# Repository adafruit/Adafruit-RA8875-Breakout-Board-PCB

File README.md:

## Adafruit RA8875 Driver Board for 40-pin TFT Touch Displays - 800x480 Max PCB

<a href="http://www.adafruit.com/products/1590"><br/>
Click here to purchase one from the Adafruit shop</a>

PCB files for the Adafruit RA8875 Driver Board for 40-pin TFT Touch Displays - 800x480 Max. Format is EagleCAD schematic and board layout
* https://www.adafruit.com/product/1590

### Description

Have you gazed longingly at large TFT displays - you know what I'm talking about here, 4", 5" or 7" TFTs with up to 800x480 pixels. Then you look at your Arduino. You love your Arduino (you really do!) but there's no way it can control a display like that, one that requires 60Hz refresh and 4 MHz pixel clocking. Heck, it doesn't even have enough pins. I suppose you could move to ARM core processors with TTL display drivers built in but you've already got all these shields working and anyways you like small micros you've got.

What if I told you there was a driver chip that could fulfill those longings? A chip that can control up 800x480 displays, and heck, a resistive touchscreen as well. All you need to give up is 5 or so SPI pins. Would you even believe me? Well, sit down because this product may shock you.

The RA8875 is a powerful TFT driver chip. It is a perfect match for any chip that wants to draw on a big TFT screen but doesn't quite have the oomph (whether it be hardware or speed). Inside is 768KB of RAM, so it can buffer the display (and depending on the screen size also have double overlaying). The interface is SPI with a very basic register read/write method of communication (no strange and convoluted packets). The chip has a range of hardware-accelerated shapes such as lines, rectangles, triangles, ellipses, built in and round-rects. There is also a built in English/European font set (see the datasheet section 7-4-1 for the font table) This makes it possible to draw fast even over SPI.

The RA8875 can also handle standard 4-wire resistive touchscreens over the same SPI interface to save you pins. There's an IRQ pin that you can use to help manage touch interrupts. The touchscreen handler isn't the most precise driver we've used, so we broke out the X/Y pins so [you can connect them up to something like the STMPE610 which is a very classy touchscreen controller](http://www.adafruit.com/products/1571).

On the PCB we have the main chip, level shifting so you can use safely with 3-5V logic. There is also a 3V regulator to provide clean power to the chip and the display. For the backlight, we put a constant-current booster that can provide 25mA or 50mA at up to 24V. The connector to the screen is a classic '40 pin' connector. All the 40-pin TFT's in the Adafruit shop are known to work well. There are other 40-pin displays that have different pinouts or backlight management and these may not work - they may even damage the driver or TFT if the boost converter pushes 24V into the display logic pins! For that reason, we only recommend the displays we've tested and sell here.

Each order comes with an assembled, tested RA8875 breakout and a stick of header. You'll also need to purchase a 40-pin TFT screen. We currently have 4.3", 5.0" and 7.0" screens available.

To get you started we've written a graphics library that handles the basic interfacing, drawing and reading functions. [Download the Adafruit RA8875 library from github](https://github.com/adafruit/Adafruit_RA8875) and [install as described in our tutorial](http://learn.adafruit.com/adafruit-all-about-arduino-libraries-install-use). Connect a 40 pin TFT to the FPC port and wire up the SPI interface to an Arduino as described in the example code. Once started you'll be able to see the graphic/text demo and then touch the screen to 'paint'. For more advanced details on what the RA8875 can do (and it can do a lot) check the datasheet.

RA8875 Driver Board for 40-pin TFT Touch Displays - 480x800 Max ([11:54](https://www.youtube.com/watch?v=PsfHcXO7IAI#t=714))

### License

Adafruit invests time and resources providing this open source design, please support Adafruit and open-source hardware by purchasing products from [Adafruit](https://www.adafruit.com)!

Designed by Limor Limor Fried/Ladyada for Adafruit Industries.

Creative Commons Attribution/Share-Alike, all text above must be included in any redistribution. See license.txt for additional details.

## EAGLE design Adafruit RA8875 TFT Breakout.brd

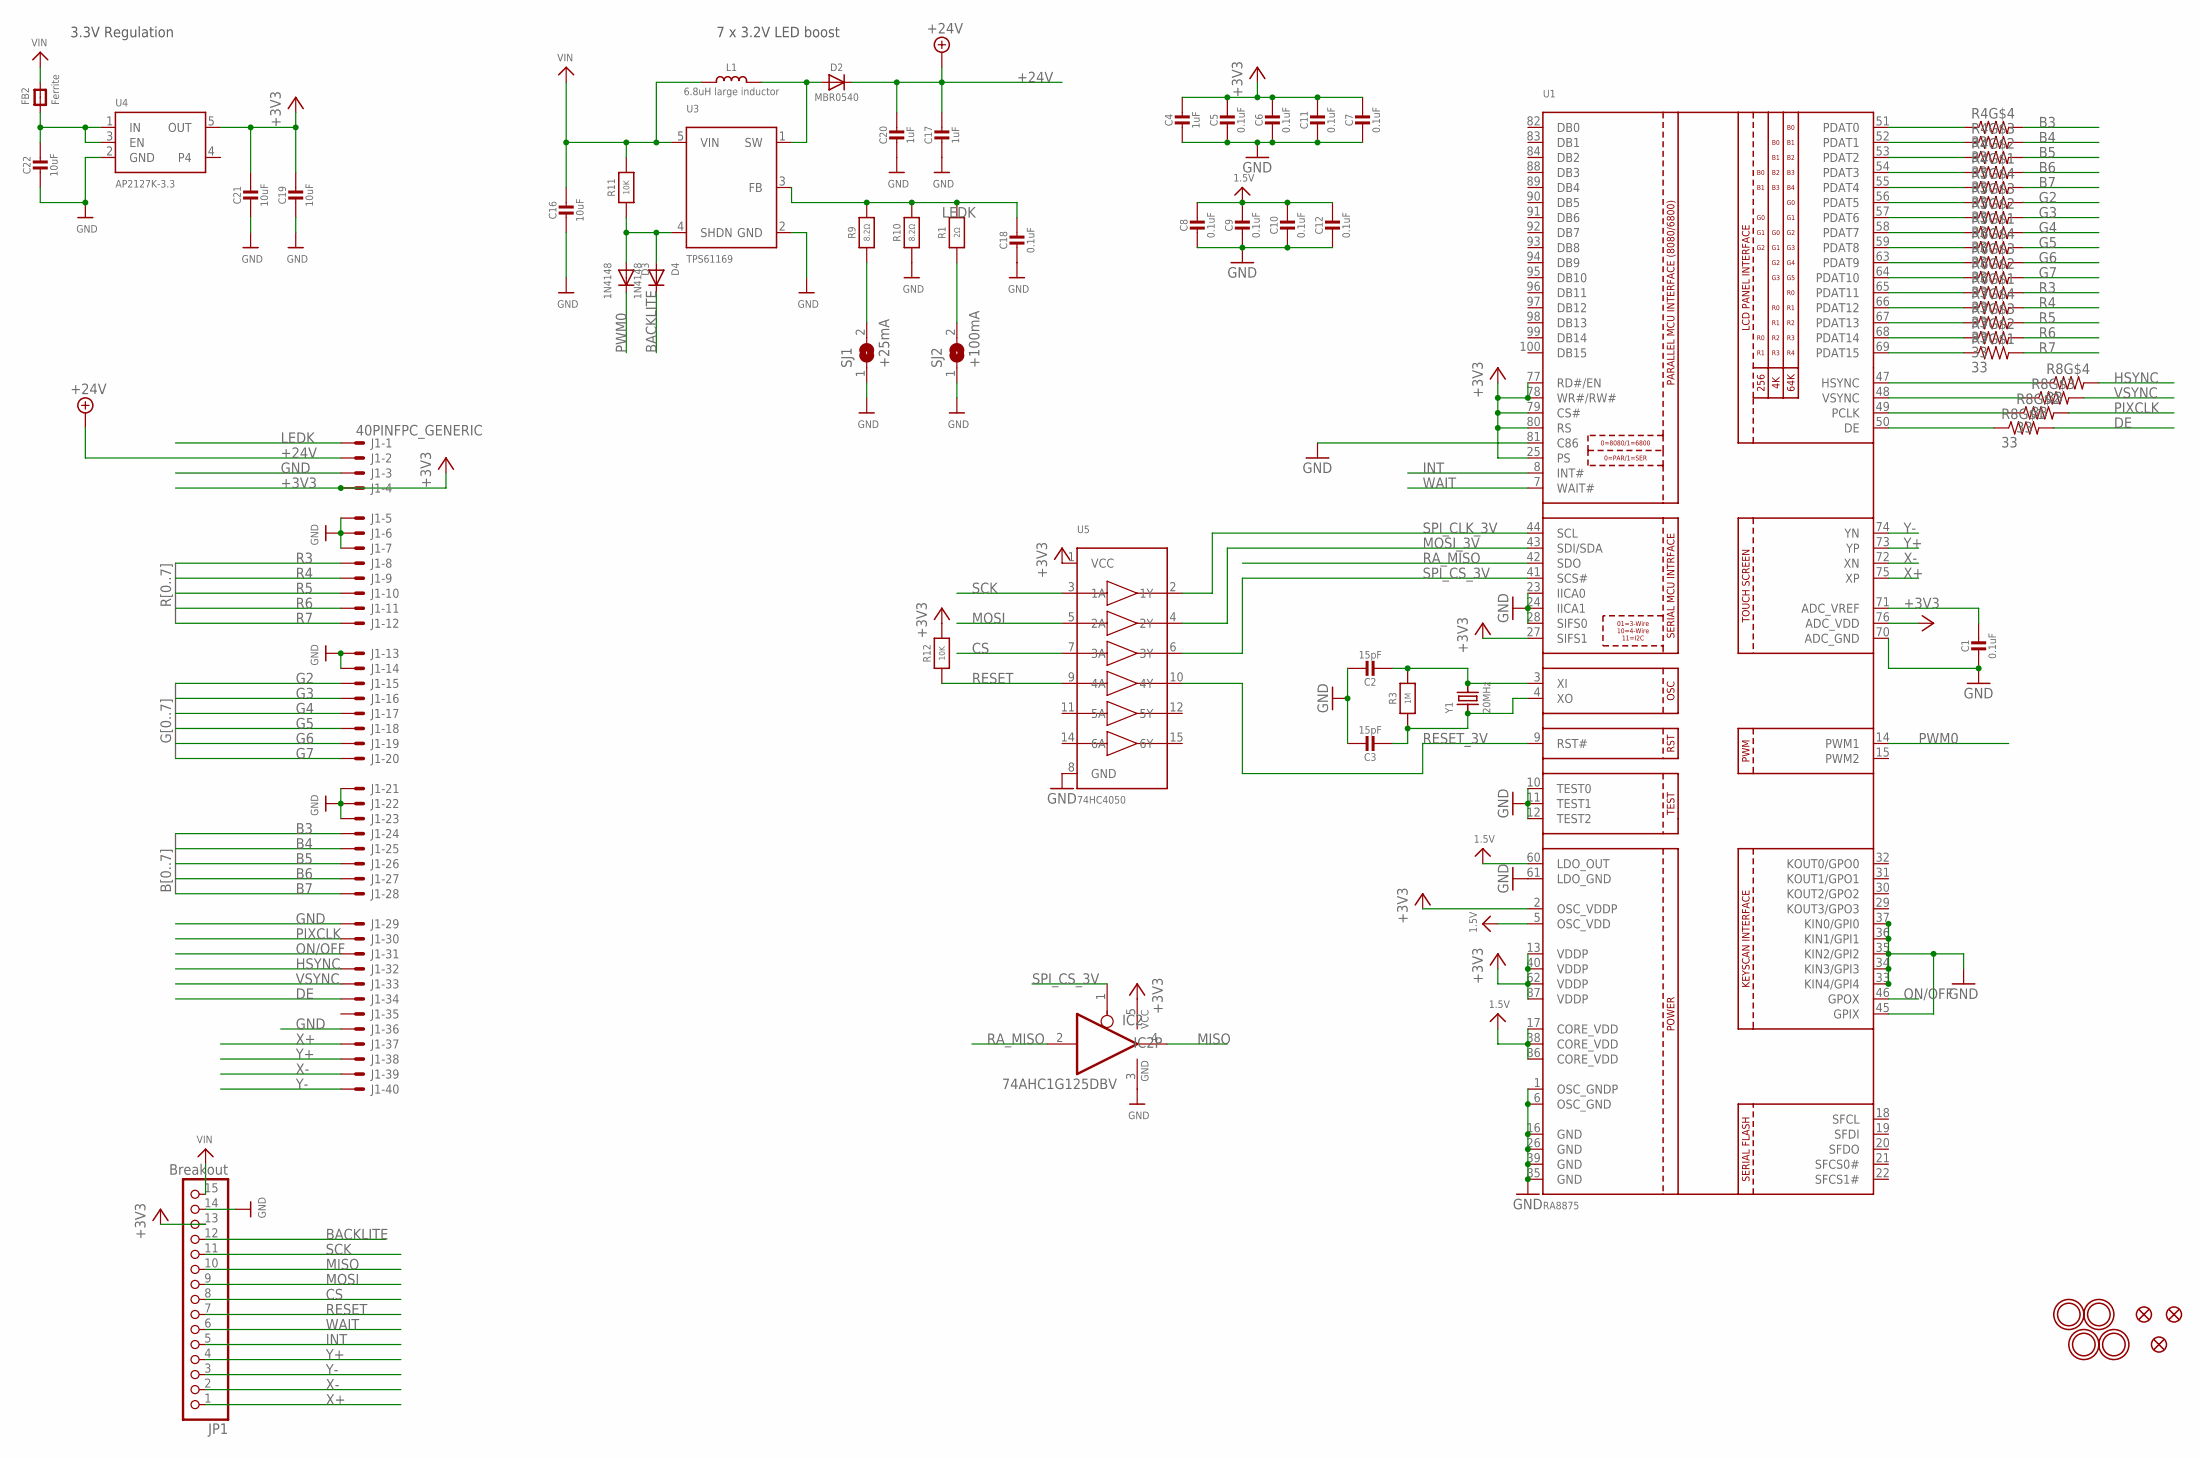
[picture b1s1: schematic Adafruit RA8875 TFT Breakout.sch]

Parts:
C1, C5, C6, C7, C8, C9, C10, C11, C12, C18: 0.1uF; 0603-NO
C2, C3: 15pF; 0603-NO
C4, C17, C20: 1uF; 0805-NO
C16, C19, C21, C22: 10uF; 0805-NO
D2: MBR0540; SOD-123
D3, D4: 1N4148; SOD-323_MINI
FB2: Ferrite; 0805-NO
FID1, FID2, FID3: FIDUCIAL_1MM
IC2: 74AHC1G125DBV; SOT23-5
J1: 40PINFPC_GENERIC; FPC_40
JP1: Breakout; 1X15-CB
L1: 6.8uH large inductor; INDUCTOR_5X5MM_NR5040_NOTHERMALS
R1: 2Ω; 0805-NO
R3: 1M; 0603-NO
R4, R5, R6, R7, R8: 33; RESPACK_4X0603
R9, R10: 8.2Ω; 0805-NO
R11, R12: 10K; 0603-NO
SJ1: +25mA; SOLDERJUMPER_ARROW_NOPASTE
SJ2: +100mA; SOLDERJUMPER_ARROW_NOPASTE
U1: RA8875; LQFP100
U3: TPS61169; SC70-5
U4: AP2127K-3.3; SOT23-5
U5: 74HC4050; TSSOP16
U$21, U$22, U$23, U$24: MOUNTINGHOLE2.5; MOUNTINGHOLE_2.5_PLATED
Y1: 20MHz; CRYSTAL_3.2X2.5

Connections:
1.5V: C8.1, C9.1, C10.1, C12.1, U1.5 (OSC_VDD), U1.17 (CORE_VDD), U1.38 (CORE_VDD), U1.60 (LDO_OUT), U1.86 (CORE_VDD)
+3V3: C4.1, C5.1, C6.1, C7.1, C11.1, C19.1, C21.1, IC2.5 (VCC), J1.4 (MS), JP1.13, R12.2, U1.2 (OSC_VDDP), U1.13 (VDDP), U1.25 (PS), U1.27 (SIFS1), U1.40 (VDDP), U1.62 (VDDP), U1.76 (ADC_VDD), U1.77 (RD#/EN), U1.78 (WR#/RW#), U1.79 (CS#), U1.80 (RS), U1.87 (VDDP), U4.5 (OUT), U5.1 (VCC)
+24V: C17.1, C20.1, D2.C, J1.2 (MS)
B3: J1.24 (MS), R4.5 (2)
B4: J1.25 (MS), R4.6 (2)
B5: J1.26 (MS), R4.7 (2)
B6: J1.27 (MS), R4.8 (2)
B7: J1.28 (MS), R5.5 (2)
BACKLITE: D4.C, JP1.12
CS: JP1.8, U5.7 (3A)
DE: J1.34 (MS), R8.8 (2)
G2: J1.15 (MS), R5.6 (2)
G3: J1.16 (MS), R5.7 (2)
G4: J1.17 (MS), R5.8 (2)
G5: J1.18 (MS), R6.5 (2)
G6: J1.19 (MS), R6.6 (2)
G7: J1.20 (MS), R6.7 (2)
GND: C1.2, C2.1, C3.1, C4.2, C5.2, C6.2, C7.2, C8.2, C9.2, C10.2, C11.2, C12.2, C16.2, C17.2, C18.2, C19.2, C20.2, C21.2, C22.2, IC2.3 (GND), J1.3 (MS), J1.5 (MS), J1.6 (MS), J1.7 (MS), J1.13 (MS), J1.14 (MS), J1.21 (MS), J1.22 (MS), J1.23 (MS), J1.29 (MS), J1.36 (MS), JP1.14, R10.1, SJ1.1, SJ2.1, U1.1 (OSC_GNDP), U1.6 (OSC_GND), U1.10 (TEST0), U1.11 (TEST1), U1.12 (TEST2), U1.16 (GND), U1.23 (IICA0), U1.24 (IICA1), U1.26 (GND), U1.28 (SIFS0), U1.33 (KIN4/GPI4), U1.34 (KIN3/GPI3), U1.35 (KIN2/GPI2), U1.36 (KIN1/GPI1), U1.37 (KIN0/GPI0), U1.39 (GND), U1.45 (GPIX), U1.61 (LDO_GND), U1.70 (ADC_GND), U1.81 (C86), U1.85 (GND), U3.2 (GND), U4.2 (GND), U5.8 (GND)
HSYNC: J1.32 (MS), R8.5 (2)
INT: JP1.5, U1.8 (INT#)
LEDK: C18.1, J1.1 (MSV), R1.2, R9.2, R10.2, U3.3 (FB)
MISO: IC2.4 (O), JP1.10
MOSI: JP1.9, U5.5 (2A)
MOSI_3V: U1.43 (SDI/SDA), U5.4 (2Y)
unnamed: D2.A, L1.P$2 (2), U3.1 (SW)
unnamed: C2.2, R3.2, U1.3 (XI), Y1.2
unnamed: C1.1, U1.71 (ADC_VREF)
unnamed: R4.4 (1), U1.51 (PDAT0)
unnamed: R4.3 (1), U1.52 (PDAT1)
unnamed: R4.2 (1), U1.53 (PDAT2)
unnamed: R4.1, U1.54 (PDAT3)
unnamed: R5.4 (1), U1.55 (PDAT4)
unnamed: R5.3 (1), U1.56 (PDAT5)
unnamed: R5.2 (1), U1.57 (PDAT6)
unnamed: R5.1, U1.58 (PDAT7)
unnamed: R6.4 (1), U1.59 (PDAT8)
unnamed: R6.3 (1), U1.63 (PDAT9)
unnamed: R6.2 (1), U1.64 (PDAT10)
unnamed: R6.1, U1.65 (PDAT11)
unnamed: R7.4 (1), U1.66 (PDAT12)
unnamed: R7.3 (1), U1.67 (PDAT13)
unnamed: R7.2 (1), U1.68 (PDAT14)
unnamed: R7.1, U1.69 (PDAT15)
unnamed: R8.1, U1.50 (DE)
unnamed: R8.2 (1), U1.49 (PCLK)
unnamed: R8.3 (1), U1.48 (VSYNC)
unnamed: R8.4 (1), U1.47 (HSYNC)
unnamed: R9.1, SJ1.2
unnamed: C22.1, FB2.1, U4.1 (IN), U4.3 (EN)
unnamed: R1.1, SJ2.2
unnamed: C3.2, R3.1, U1.4 (XO), Y1.1
ON/OFF: J1.31 (MS), U1.46 (GPOX)
PIXCLK: J1.30 (MS), R8.7 (2)
PWM0: D3.C, U1.14 (PWM1)
R3: J1.8 (MS), R6.8 (2)
R4: J1.9 (MS), R7.5 (2)
R5: J1.10 (MS), R7.6 (2)
R6: J1.11 (MS), R7.7 (2)
R7: J1.12 (MS), R7.8 (2)
RA_MISO: IC2.2 (I), U1.42 (SDO)
RESET: JP1.7, R12.1, U5.9 (4A)
RESET_3V: U1.9 (RST#), U5.10 (4Y)
SCK: JP1.11, U5.3 (1A)
SHDN: D3.A, D4.A, R11.1, U3.4 (SHDN)
SPI_CLK_3V: U1.44 (SCL), U5.2 (1Y)
SPI_CS_3V: IC2.1 (OE), U1.41 (SCS#), U5.6 (3Y)
VIN: C16.1, FB2.2, JP1.15, L1.P$1 (1), R11.2, U3.5 (VIN)
VSYNC: J1.33 (MS), R8.6 (2)
WAIT: JP1.6, U1.7 (WAIT#)
X+: J1.37 (MS), JP1.1, U1.75 (XP)
X-: J1.39 (MS), JP1.2, U1.72 (XN)
Y+: J1.38 (MS), JP1.4, U1.73 (YP)
Y-: J1.40 (MS), JP1.3, U1.74 (YN)

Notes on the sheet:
7 x 3.2V LED boost
3.3V Regulation

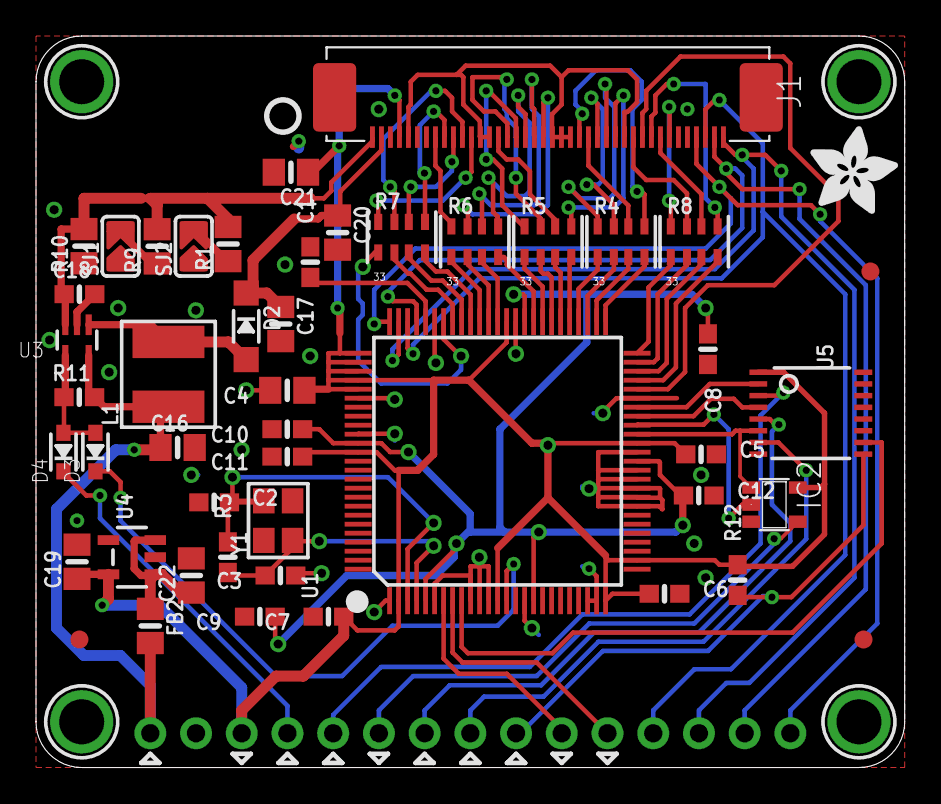
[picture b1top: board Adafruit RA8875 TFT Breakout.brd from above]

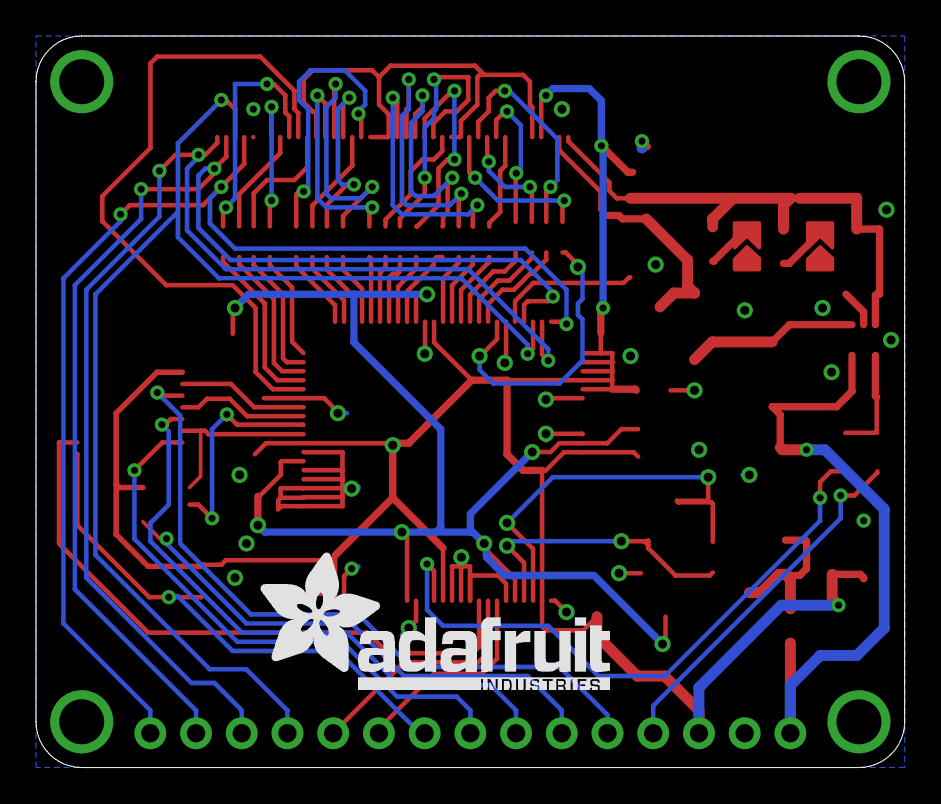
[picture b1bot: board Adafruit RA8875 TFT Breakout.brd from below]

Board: 2 copper layers, 48.3 x 40.6 mm, 79 parts (4 on the bottom side), 73 nets.

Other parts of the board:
PLABEL0: PLABEL0
PLABEL1: PLABEL1
PLABEL2: PLABEL2
PLABEL3: PLABEL3
PLABEL4: PLABEL4
PLABEL5: PLABEL5
PLABEL6: PLABEL6
PLABEL7: PLABEL7
PLABEL8: PLABEL8
PLABEL9: PLABEL9
PLABEL10: PLABEL10
PLABEL11: PLABEL11
PLABEL12: PLABEL12
PLABEL13: PLABEL13
PLABEL14: PLABEL14
PLABEL15: PLABEL15
PLABEL16: PLABEL16
PLABEL17: PLABEL17
PLABEL18: PLABEL18
PLABEL19: PLABEL19
PLABEL20: PLABEL20
PLABEL21: PLABEL21
PLABEL22: PLABEL22
PLABEL23: PLABEL23
U$18: ADAFRUIT_5MM
U$25: ADAFRUIT_TEXT_20MM
U$30: PCBFEAT-REV-040

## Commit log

2014-05-02 init
2014-05-02 read
2018-11-29 Add schematic PDF
2019-03-20 Updated to the latest board and schematic
2019-03-20 Renamed files to original names
2019-07-17 updated to use cookiecutter for pcb repos
2023-09-14 Update board files to latest rev
2023-09-14 Update readme image

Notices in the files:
parts and their libraries:
microbuilder: This work is placed in the public domain, and may be freely used for commercial and non-commercial work with the following conditions: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
